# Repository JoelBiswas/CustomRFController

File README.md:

# Custom Star Wars RF Controller
This repository contains the files to build a custom RF controller in the shape of the Rebel Alliance Logo from Star Wars. The controller consists of two joysticks, six buttons, and is controlled by an ESP32. This project was created entirely by me for Hack Club's Highway to Undercity event. My plan is to test this device by using to control an [R2-D2 droid that I designed](https://github.com/JoelBiswas/r2d2/tree/main) for the same Hack Club event earlier this summer.

## Bill of Materials
View the Bill of Materials [here](https://docs.google.com/spreadsheets/d/1eimf_XqeCwkksVUzqHQLZJRxSmD6-AT-35apM8Ljc3Q/edit?usp=sharing)

## The Beginning
The idea for this project came after finishing my last project, an R2-D2 droid controlled with a PS3 controller. I thought that it would be interesting to make my own Star Wars-themed RF transmitter to control the droid with. I hoped that this would provide the robot with much greater range than a Bluetooth-based controller. This project felt perfect as I was looking to start a project that expands my electrical skills. My last project was heavily focused on CAD, so I wanted this project to be more focused on wiring schematic and PCB design. Like the droid, this project is also made for Hack Club's Highway to Undercity event, which provides high school students with grants to build their dream projects.

## About the Controller
The controller consists of two main parts: the PCB and the case. The PCB consists of an ESP32, two MP1584 buck converters, two KY-023 Joystick Modules, six push buttons, and an nRF24L01+ PA/LNA RF Module. It is powered by a 2S LiPo battery that connects to the PCB using a Deans Connector. The case is 3D-printable and houses the battery and PCB. The two joysticks are labeled LS and RS, and the buttons are labeled A, B, X, Y, 1, and 2. An antenna on the PCB extends up through a hole in the top of the case in order to transmit the RF signals.

## Overview of this Repo
**CAD** - Contains the CAD files for the controller, along with images taken from OnShape. <br>
**STLs** - Contains files for each part that needs to be 3D printed <br>
**Print** - Contains the 3d print files for the Flashforge Adventurer 5M <br>
**Electrical** - Contains files from KiCAD for the controller's wiring schematic, custom symbols, custom footprints, and PCB <br>
**Code** - Currently empty but will eventually contain the code for sending RF signals <br>
**JOURNAL.md** - Contains an overview of exactly how I designed and built this robot <br>
**BOM.csv** - A bill of materials for this project in CSV format <br>

## Designing the Robot
Click [here](https://cad.onshape.com/documents/af772411fd2681a1311b7be6/w/e5e3a94108ce63d65661e1b4/e/943c3c2dcbac8496e1ce6b2c?renderMode=0&uiState=685208efd1f4554e80aaa1d0) to view the Onshape document for this project. The electronic design was done in KiCAD.

## General Steps for Assembly
1. 3D print each of the files in the STLs folder. The case top and bottom should be printed in orange PLA, and the button should be printed six times in black PLA.
2. Place the LiPo battery into the inserts in the case
3. Place the PCB over the battery on the standoffs. Plug the battery into the Deans connector on the PCB
4. Bolt in the top of the case using an M3 bolt on each side
5. Hot glue the 3D printed button onto the PCB buttons

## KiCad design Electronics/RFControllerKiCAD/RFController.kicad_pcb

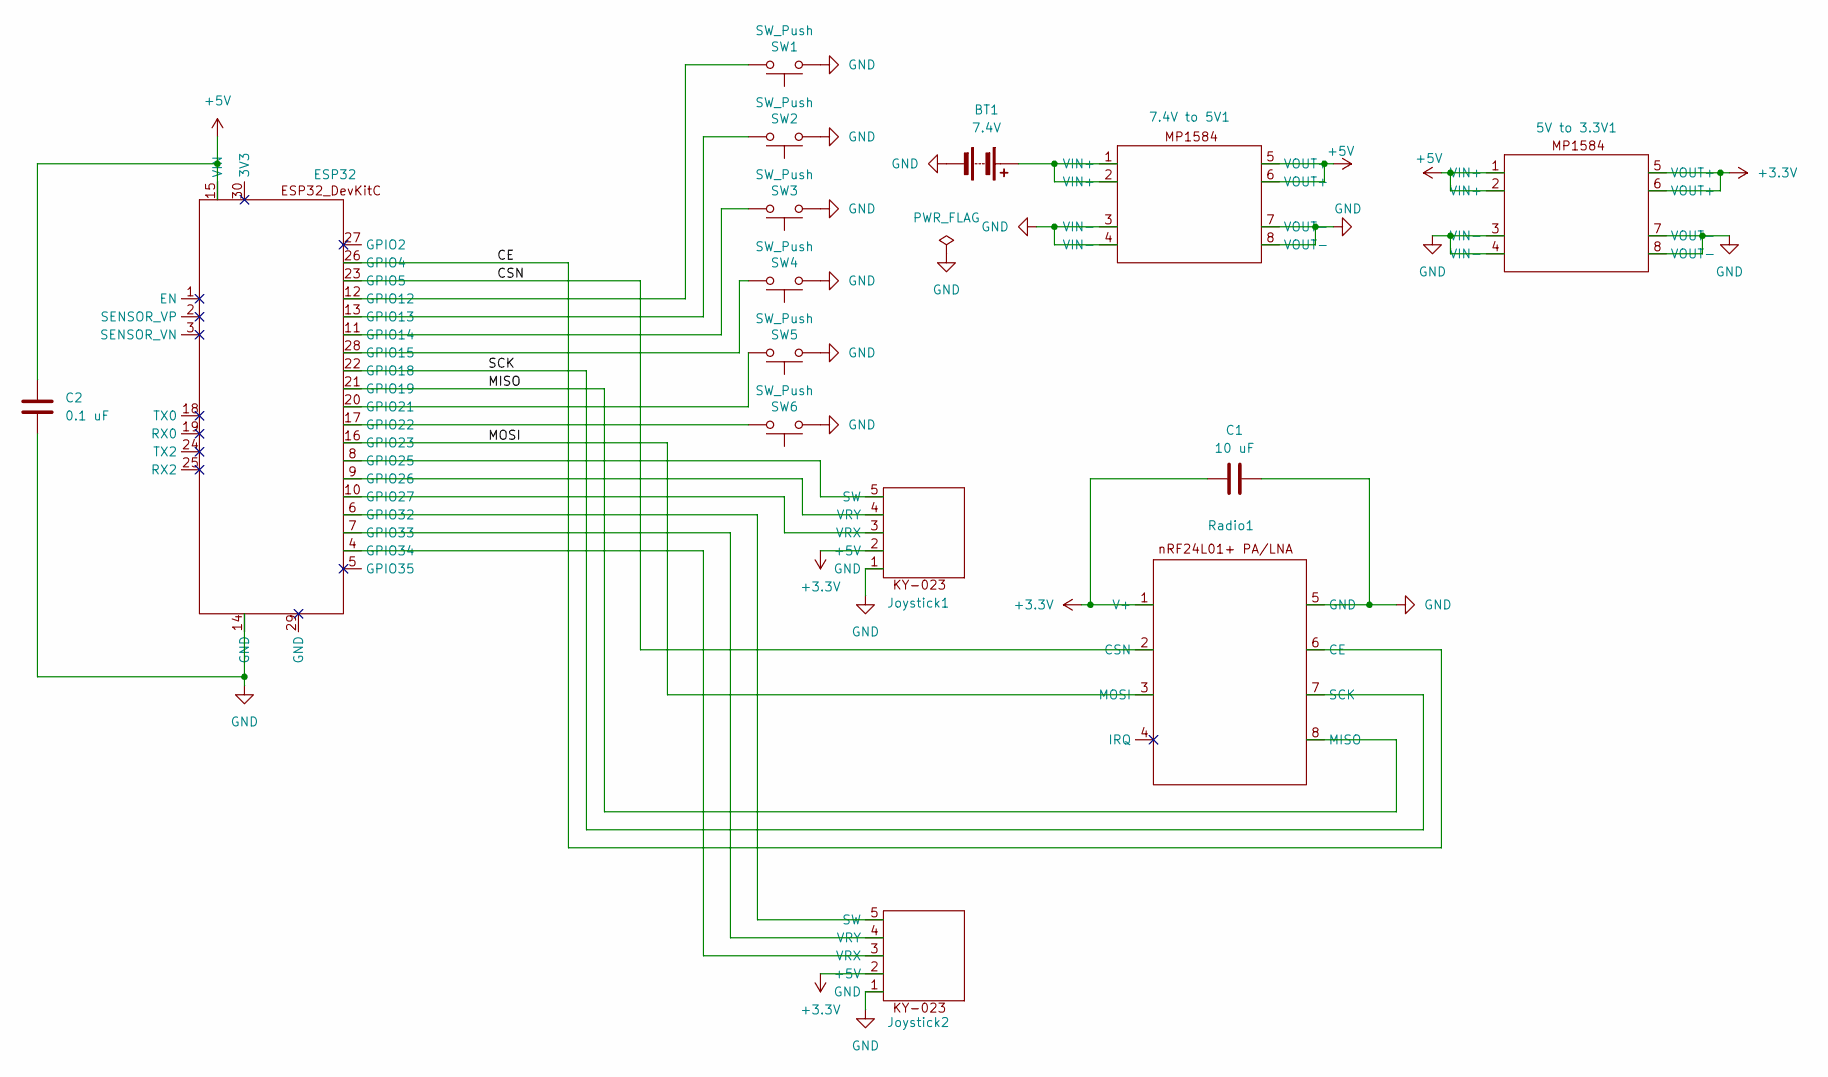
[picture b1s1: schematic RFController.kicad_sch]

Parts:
5V to 3.3V1, 7.4V to 5V1: MP1584_Module
BT1: 7.4V; Deans_Connector
C1: 10 uF; C_Disc_D4.3mm_W1.9mm_P5.00mm
C2: 0.1 uF; C_Disc_D4.3mm_W1.9mm_P5.00mm
ESP32: ESP32_DevKitC_30
Joystick1, Joystick2: KY-023_Module
Radio1: NRF24L01_PA_LNA
SW1, SW2, SW3, SW4, SW5, SW6: SW_Push; SW_PUSH_6mm

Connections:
+3.3V: 5V to 3.3V1.5 (VOUT+), 5V to 3.3V1.6 (VOUT+), C1.1, Joystick1.2 (+5V), Joystick2.2 (+5V), Radio1.1 (V+)
+5V: 5V to 3.3V1.1 (VIN+), 5V to 3.3V1.2 (VIN+), 7.4V to 5V1.5 (VOUT+), 7.4V to 5V1.6 (VOUT+), C2.1, ESP32.15 (VIN)
/CE: ESP32.26 (GPIO4), Radio1.6 (CE)
/CSN: ESP32.23 (GPIO5), Radio1.2 (CSN)
/MISO: ESP32.21 (GPIO19), Radio1.8 (MISO)
/MOSI: ESP32.16 (GPIO23), Radio1.3 (MOSI)
/SCK: ESP32.22 (GPIO18), Radio1.7 (SCK)
GND: 5V to 3.3V1.3 (VIN-), 5V to 3.3V1.4 (VIN-), 5V to 3.3V1.7 (VOUT-), 5V to 3.3V1.8 (VOUT-), 7.4V to 5V1.3 (VIN-), 7.4V to 5V1.4 (VIN-), 7.4V to 5V1.7 (VOUT-), 7.4V to 5V1.8 (VOUT-), BT1.2 (-), C1.2, C2.2, ESP32.14 (GND), Joystick1.1 (GND), Joystick2.1 (GND), Radio1.5 (GND), SW1.1, SW2.1, SW3.1, SW4.1, SW5.1, SW6.1
unnamed: 7.4V to 5V1.1 (VIN+), 7.4V to 5V1.2 (VIN+), BT1.1 (+)
unnamed: ESP32.12 (GPIO12), SW1.2
unnamed: ESP32.13 (GPIO13), SW2.2
unnamed: ESP32.11 (GPIO14), SW3.2
unnamed: ESP32.28 (GPIO15), SW4.2
unnamed: ESP32.20 (GPIO21), SW5.2
unnamed: ESP32.17 (GPIO22), SW6.2
unnamed: ESP32.8 (GPIO25), Joystick1.5 (SW)
unnamed: ESP32.9 (GPIO26), Joystick1.4 (VRY)
unnamed: ESP32.10 (GPIO27), Joystick1.3 (VRX)
unnamed: ESP32.6 (GPIO32), Joystick2.5 (SW)
unnamed: ESP32.7 (GPIO33), Joystick2.4 (VRY)
unnamed: ESP32.4 (GPIO34), Joystick2.3 (VRX)

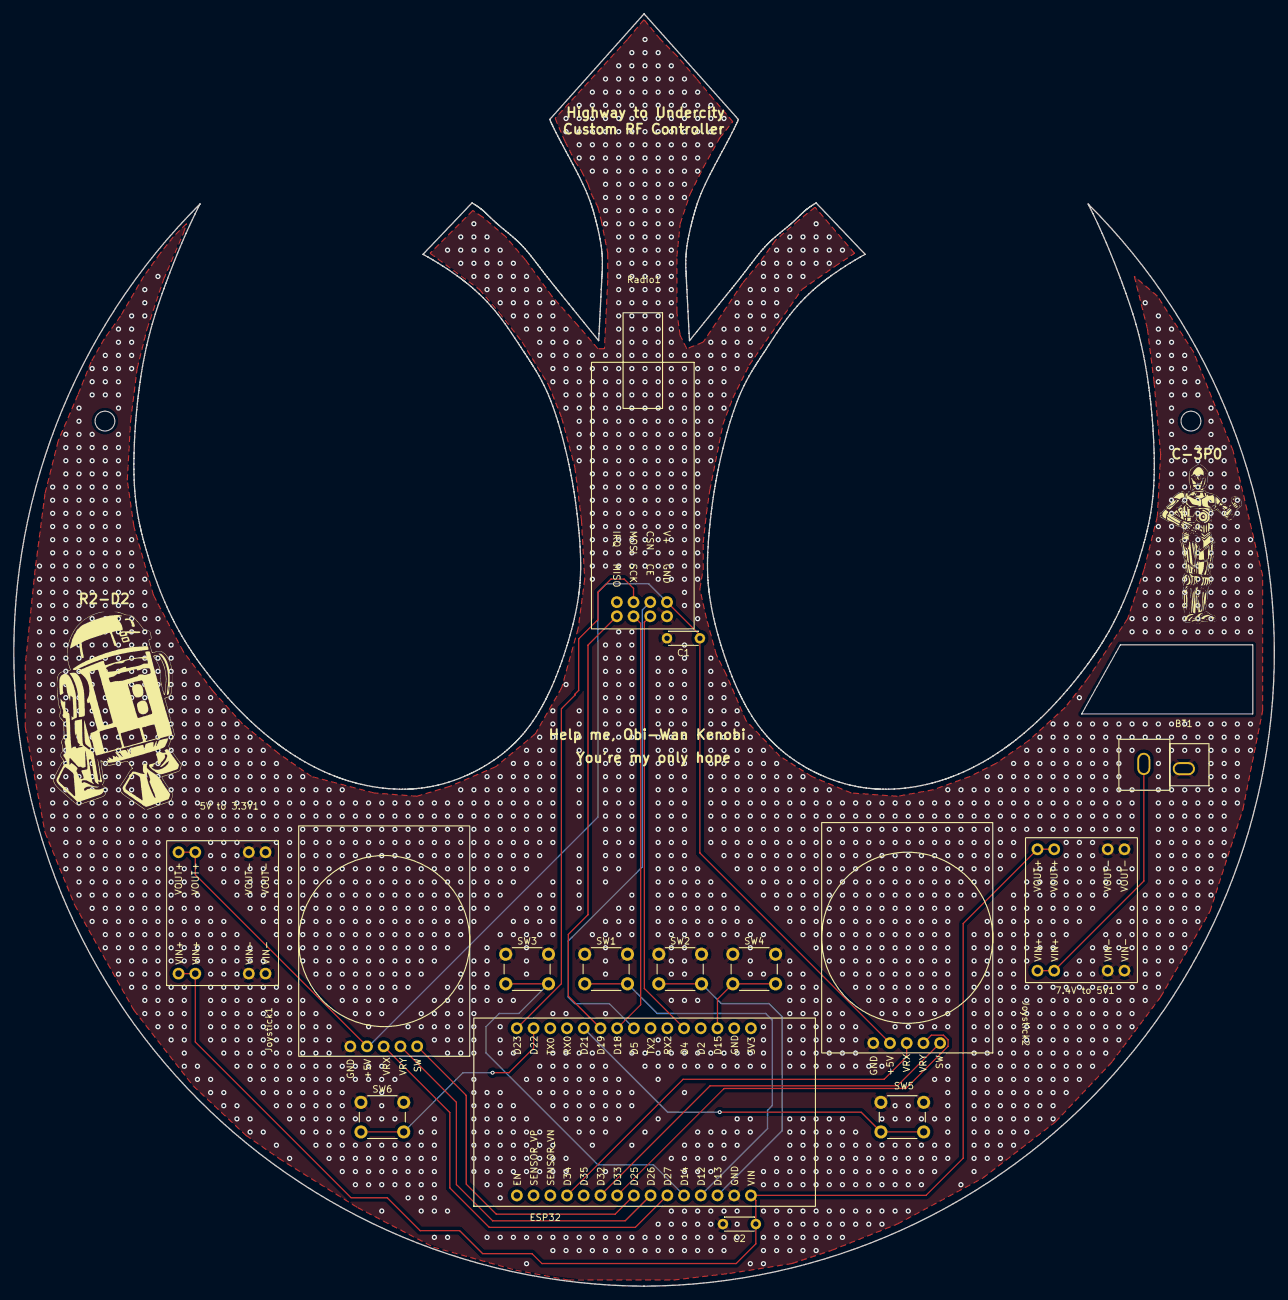
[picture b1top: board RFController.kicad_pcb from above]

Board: 2 copper layers, 191.5 x 193.3 mm, 17 parts (0 on the bottom side), 21 nets.

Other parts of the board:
C-3P0: LOGO
R2-D2: LOGO

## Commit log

2025-06-17 Added Files
2025-06-17 Added .gitignore
2025-06-17 Removed .DS_Store
2025-07-22 Updated STLs
2025-07-22 Updated Print
